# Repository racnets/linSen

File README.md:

# linSen (huch linear sensor array - HUB)

## Description
Layout and schematics for the linear sensor array TSL1401CL connected to STM32F103 ARM-Cortex M3.

Designed with [eagle](http://www.cadsoftusa.com/eagle-pcb-design-software) 

### Datasheets
* [TSL1401CL](http://www.ams.com/eng/content/download/250163/975677/file/TSL1401CL.pdf)
* [STM32F103](http://www.st.com/st-web-ui/static/active/en/resource/technical/document/datasheet/CD00161566.pdf)

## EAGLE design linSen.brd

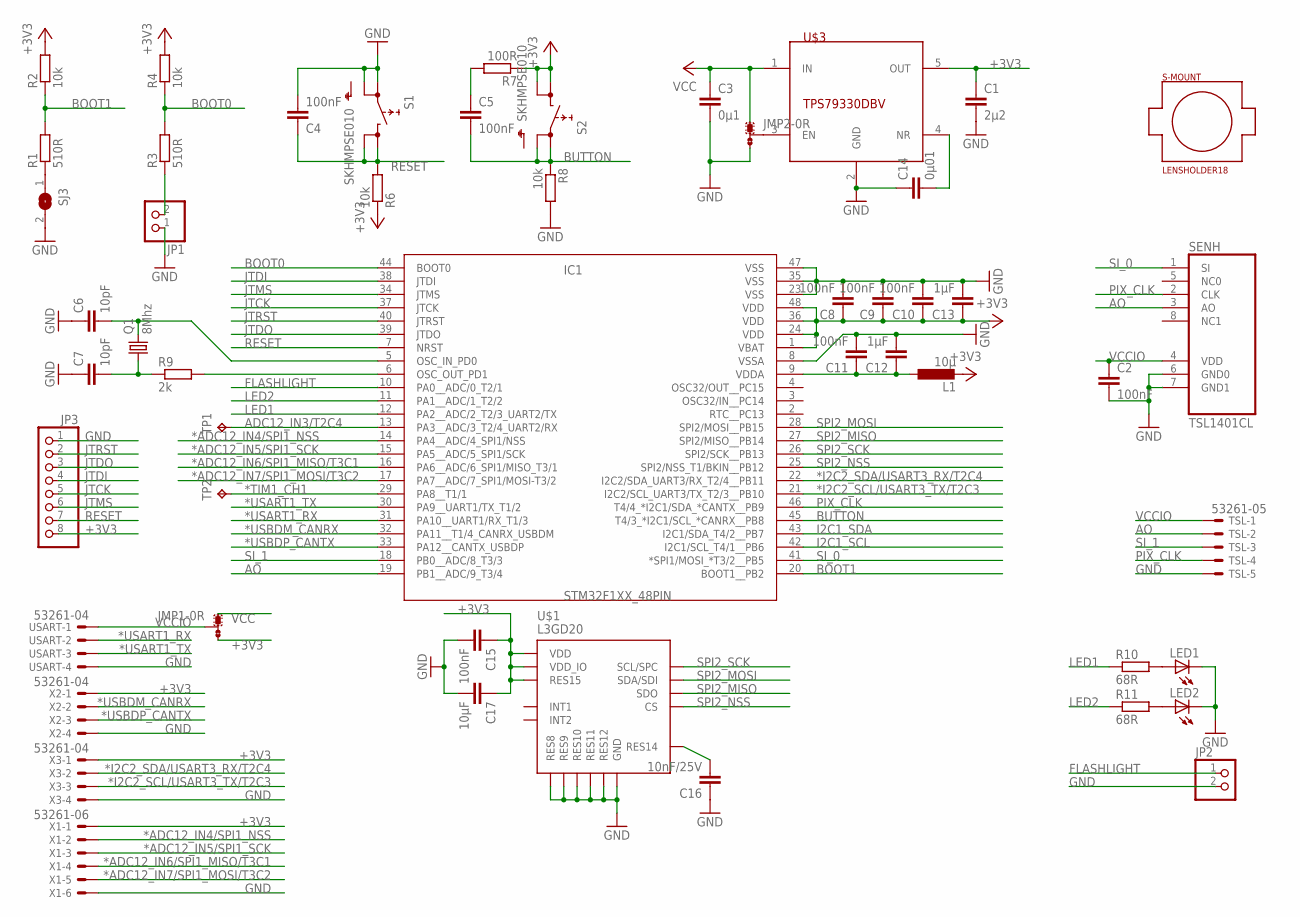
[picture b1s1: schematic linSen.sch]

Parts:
C1: 2µ2; C0805
C2, C4, C5, C8, C9, C10, C11, C15: 100nF; C0603
C3: 0µ1; C0603
C6, C7: 10pF; C0603
C12, C13: 1µF; C0603
C14: 0µ01; C0603
C16: 10nF/25V; C0603
C17: 10µF; C0603
IC1: STM32F1XX_48PIN; LQFP48_PACKAGE
JMP1, JMP2: 0R-JUMPB; B0R-JMP
JP1: PINHD-1X2/90; 1X02/90
JP2: PINHD-1X2; 1X02
JP3: PINHD-1X8/SMD; SMD-PAD-08
L1: 10µ; L2012C
LED1, LED2: LEDCHIPLED_0603; CHIPLED_0603
Q1: 8Mhz; SM49
R1, R3: 510R; R0603
R2, R4, R6, R8: 10k; R0603
R7: 100R; R0603
R9: 2k; R0603
R10, R11: 68R; R0603
S1, S2: SKHMPSE010; SKHMPXE010
S-MOUNT: LENSHOLDER18; SMOUNT18
SENH: TSL1401CL
SJ3: SJ
TP1, TP2: TPB1,27; B1,27
TSL: 53261-05
U$1: L3GD20; LGA-16
U$3: TPS79330DBV; SOT23-5
USART: 53261-04
X1: 53261-06
X2, X3: 53261-04

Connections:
*ADC12_IN4/SPI1_NSS: IC1.14 (PA4__ADC/4_SPI1/NSS), X1.2
*ADC12_IN5/SPI1_SCK: IC1.15 (PA5__ADC/5_SPI1/SCK), X1.3
*ADC12_IN6/SPI1_MISO/T3C1: IC1.16 (PA6__ADC/6_SPI1/MISO_T3/1), X1.4
*ADC12_IN7/SPI1_MOSI/T3C2: IC1.17 (PA7__ADC/7_SPI1/MOSI-T3/2), X1.5
*I2C2_SCL/USART3_TX/T2C3: IC1.21 (I2C2/SCL_UART3/TX_T2/3__PB10), X3.3
*I2C2_SDA/USART3_RX/T2C4: IC1.22 (I2C2/SDA_UART3/RX_T2/4__PB11), X3.2
*TIM1_CH1: IC1.29 (PA8__T1/1), TP2.TP
*USART1_RX: IC1.31 (PA10__UART1/RX_T1/3), USART.2
*USART1_TX: IC1.30 (PA9__UART1/TX_T1/2), USART.3
*USBDM_CANRX: IC1.32 (PA11__T1/4_CANRX_USBDM), X2.2
*USBDP_CANTX: IC1.33 (PA12__CANTX_USBDP), X2.3
+3V3: C1.1, C8.1, C9.1, C10.1, C13.1, C15.1, C17.1, IC1.1 (VBAT), IC1.24 (VDD), IC1.36 (VDD), IC1.48 (VDD), JMP1.3, JP3.8, L1.2, R2.2, R4.2, R6.1, R7.1, S2.3 (2.1), S2.4 (2.2), U$1.P$1 (VDD_IO), U$1.P$15 (RES15), U$1.P$16 (VDD), U$3.5 (OUT), X1.1, X2.1, X3.1
ADC12_IN3/T2C4: IC1.13 (PA3__ADC/3_T2/4_UART2/RX), TP1.TP
AO: IC1.19 (PB1__ADC/9_T3/4), SENH.3 (AO), TSL.2
BOOT0: IC1.44 (BOOT0), R3.2, R4.1
BOOT1: IC1.20 (BOOT1__PB2), R1.2, R2.1
BUTTON: C5.2, IC1.45 (T4/3_*I2C1/SCL_*CANRX__PB8), R8.1, S2.1 (1.1), S2.2 (1.2)
FLASHLIGHT: IC1.10 (PA0__ADC/0_T2/1), JP2.1
GND: C1.2, C2.2, C3.2, C4.2, C6.1, C7.1, C8.2, C9.2, C10.2, C11.2, C12.2, C13.2, C14.1, C15.2, C16.1, C17.2, IC1.8 (VSSA), IC1.23 (VSS), IC1.35 (VSS), IC1.47 (VSS), JMP2.3, JP1.1, JP2.2, JP3.1, LED1.C, LED2.C, R8.2, S1.1 (1.1), S1.2 (1.2), SENH.6 (GND0), SENH.7 (GND1), SJ3.2, TSL.5, U$1.P$8 (RES8), U$1.P$9 (RES9), U$1.P$10 (RES10), U$1.P$11 (RES11), U$1.P$12 (RES12), U$1.P$13 (GND), U$3.2 (GND), USART.4, X1.6, X2.4, X3.4
I2C1_SCL: IC1.42 (I2C1/SCL_T4/1__PB6)
I2C1_SDA: IC1.43 (I2C1/SDA_T4/2__PB7)
JTCK: IC1.37 (JTCK), JP3.5
JTDI: IC1.38 (JTDI), JP3.4
JTDO: IC1.39 (JTDO), JP3.3
JTMS: IC1.34 (JTMS), JP3.6
JTRST: IC1.40 (JTRST), JP3.2
LED1: IC1.12 (PA2__ADC/2_T2/3_UART2/TX), R10.1
LED2: IC1.11 (PA1__ADC/1_T2/2), R11.1
unnamed: JP1.2, R3.1
unnamed: R1.1, SJ3.1
unnamed: C6.2, IC1.5 (OSC_IN_PD0), Q1.2
unnamed: C16.2, U$1.P$14 (RES14)
unnamed: C7.2, Q1.1, R9.1
unnamed: C5.1, R7.2
unnamed: IC1.6 (OSC_OUT_PD1), R9.2
unnamed: C14.2, U$3.4 (NR)
unnamed: JMP2.2, U$3.3 (EN)
unnamed: C11.1, C12.1, IC1.9 (VDDA), L1.1
unnamed: LED1.A, R10.2
unnamed: LED2.A, R11.2
PIX_CLK: IC1.46 (T4/4_*I2C1/SDA_*CANTX__PB9), SENH.2 (CLK), TSL.4
RESET: C4.1, IC1.7 (NRST), JP3.7, R6.2, S1.3 (2.1), S1.4 (2.2)
SI_0: IC1.41 (*SPI1/MOSI_*T3/2__PB5), SENH.1 (SI)
SI_1: IC1.18 (PB0__ADC/8_T3/3), TSL.3
SPI2_MISO: IC1.27 (SPI2/MISO__PB14), U$1.P$4 (SDO)
SPI2_MOSI: IC1.28 (SPI2/MOSI__PB15), U$1.P$3 (SDA/SDI)
SPI2_NSS: IC1.25 (SPI2/NSS_T1/BKIN__PB12), U$1.P$5 (CS)
SPI2_SCK: IC1.26 (SPI2/SCK__PB13), U$1.P$2 (SCL/SPC)
VCC: C3.1, JMP1.1, JMP2.1, U$3.1 (IN)
VCCIO: C2.1, JMP1.2, SENH.4 (VDD), TSL.1, USART.1

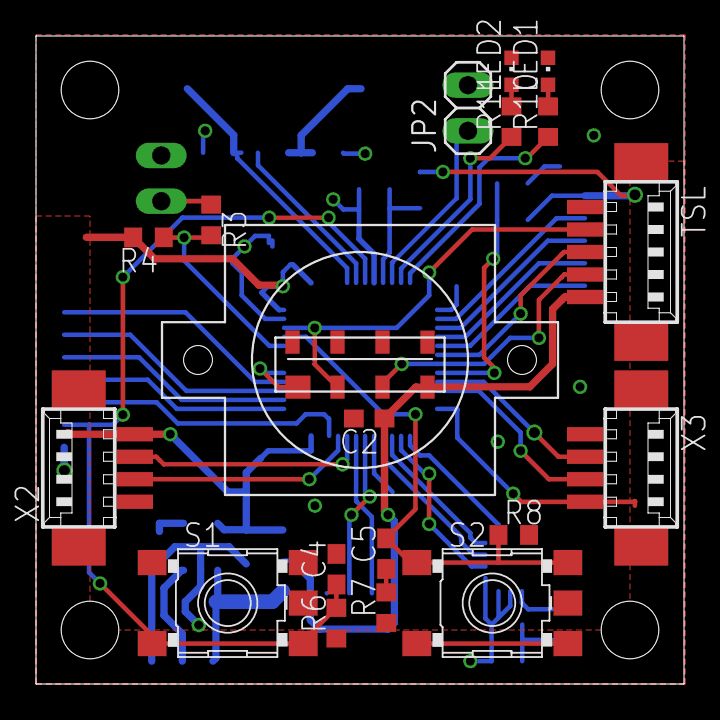
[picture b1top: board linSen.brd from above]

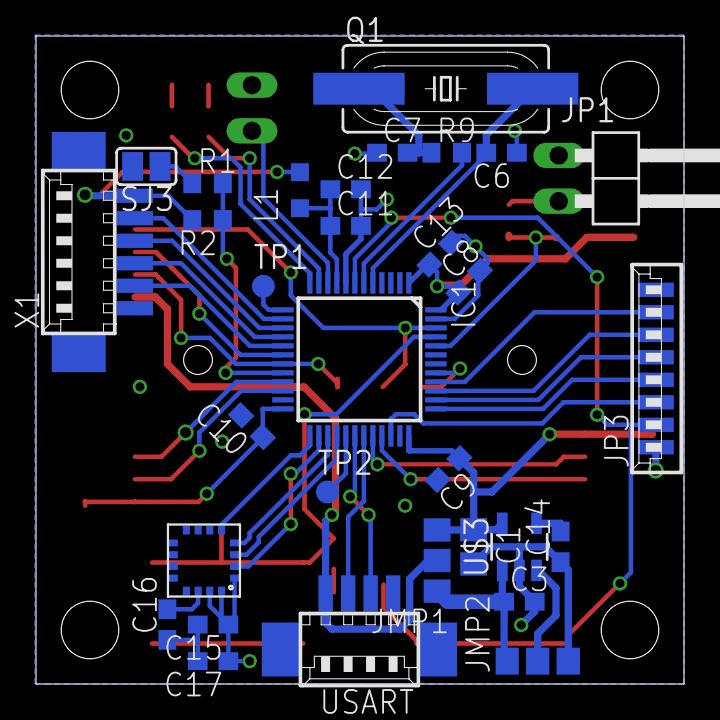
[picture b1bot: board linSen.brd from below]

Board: 2 copper layers, 36.0 x 36.0 mm, 51 parts (31 on the bottom side), 48 nets.
